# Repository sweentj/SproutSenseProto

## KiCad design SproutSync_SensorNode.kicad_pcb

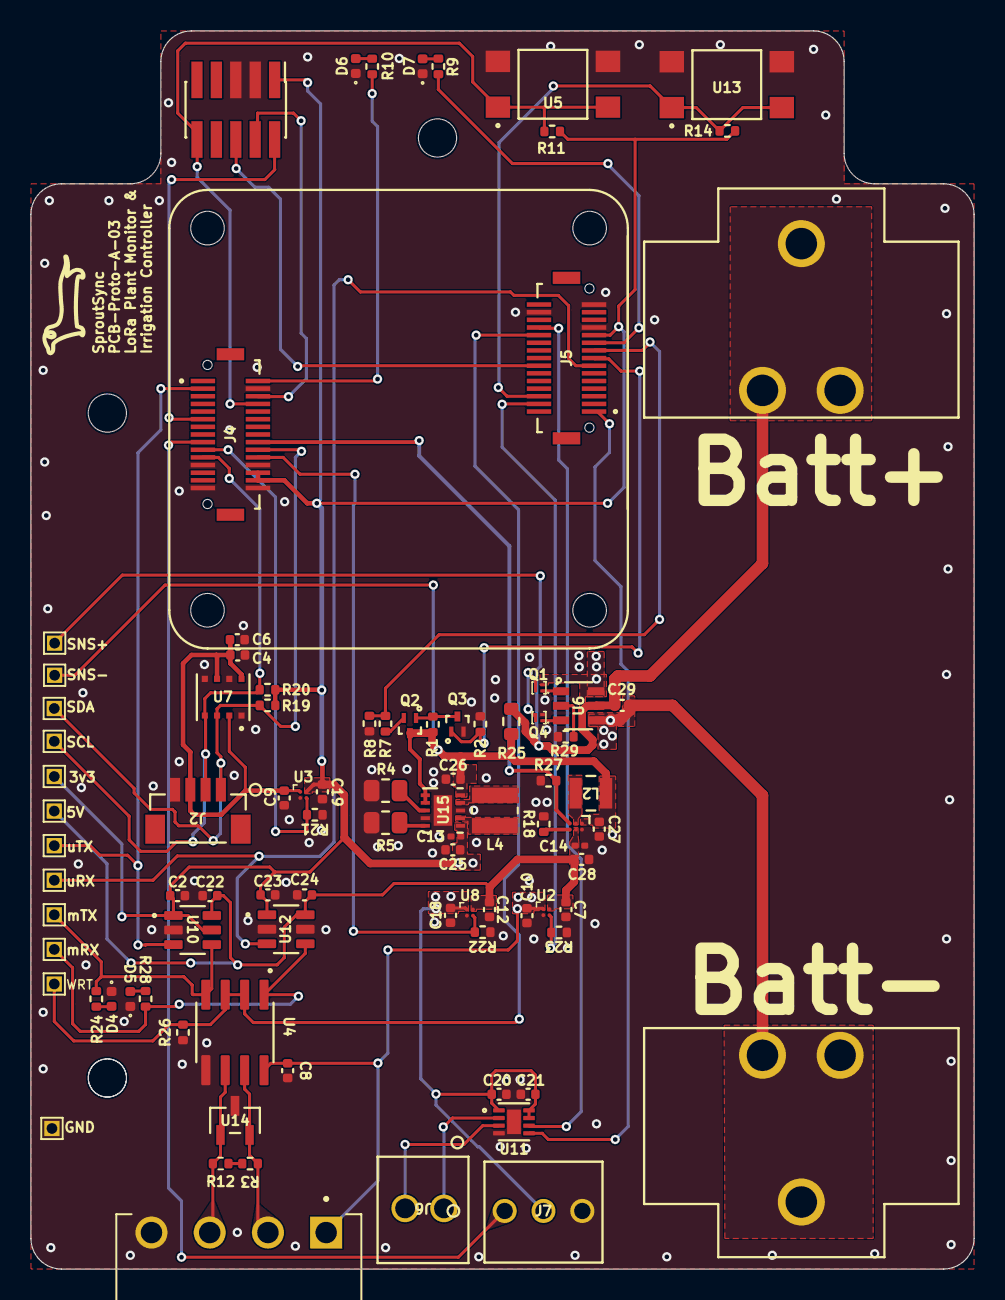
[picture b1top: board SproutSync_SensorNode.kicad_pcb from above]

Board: 2 copper layers, 61.7 x 81.0 mm, 91 parts (0 on the bottom side), 53 nets.

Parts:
C2, C8, C9, C10, C18, C22, C23, C24, C29: 1uF; C_0402_1005Metric
C4, C6, C20, C21: 100nF; C_0402_1005Metric
C7, C12, C19, C25, C26, C27, C28: 22uF; C_0402_1005Metric
C13, C14: 10n; C_0201_0603Metric
D4, D5, D6, D7: B2841USD; LED_0402_1005Metric
J1: TBP02R1-381-04BE; CUI_TBP02R1-381-04BE
J2: BM04B-SRSS-TB; CONN4_BM04B-SRSS_JST
J3, J9: Conn_01x01_Socket; BAT_247
J4, J5: 10132797-031100LF; AMPHENOL_10132797-031100LF
J6: OSTVN02A150; CONN_OSTVN02A150_OST
J7: Conn_01x03; CONN_A-6373-03A_MOL
J8: Conn_ARM_JTAG_SWD_10; PinHeader_2x05_P1.27mm_Vertical_SMD
L2: DFE252012P-1R0M=P2
L4: 2.2u; IND_VLS3012CX-2R2M-1
Q1, Q4: CSD15380F3T; PICOSTAR-3_L0.7-W0.6-P0.35-TL
Q2: SSM3J35MFV; VESM_TOS
Q3: SSM3K16FV; VESM_TOS
R1, R2: 47k; R_0402_1005Metric
R3: 120; R_0402_1005Metric
R4: 36.5k; R_0805_2012Metric
R5: 16.2k; R_0805_2012Metric
R7: 20k; R_0402_1005Metric
R8: 18k; R_0402_1005Metric
R9, R10: 1k; R_0402_1005Metric
R11, R14, R19, R20, R21, R22, R23, R24, R27, R28: 4.7k; R_0402_1005Metric
R12: 0; R_0402_1005Metric
R18: 7.5k; R_0402_1005Metric
R25: 100m; R_0603_1608Metric
R26: 9.31k; R_0402_1005Metric
R29: 330; R_0402_1005Metric
TP1, TP2, TP5, TP6, TP7, TP8, TP9, TP10, TP11, TP12, TP14, TP15: TestPoint; TestPoint_THTPad_1.0x1.0mm_Drill0.5mm
U2, U3, U8: TPS22914BYFPR; YFP4_TEX
U4: SN65HVD3082EDR; SOIC127P599X175-8N
U5, U13: TL3305AF260QG; SW_TL3305AF260QG
U6: S-8240ADZ-M6T1U; SOT-23-6_L2.9-W1.6-P0.95-LS2.8-TL
U7: BME688; IC_BME688
U10, U12: SN74LVC1T45DBVR; SOT95P280X145-6N
U11: DRV8838DSGR; SON50P200X200X80-9N
U14: CDSOT23-SM712; SOT_SM712
U15: TPS63900DSKR; DSK0010A
U16: TPS61299YBHR; DSBGA6_YBH_TEX

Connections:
+3V3: C2.1, C13.1, C19.1, C23.1, C25.1, J4.17, J4.18, J5.11, J8.1 (VTref), R11.2, R14.2, R19.2, R20.2, TP14.1 (1_1), U3.A2 (VIN), U10.1 (VCCA), U10.5 (DIR), U12.1 (VCCA), U15.6 (VOUT)
+5V: C7.1, C12.1, C14.1, C22.1, C24.1, C28.1, TP15.1 (1_1), U2.A2 (VIN), U8.A2 (VIN), U10.6 (VCCB), U12.6 (VCCB), U16.B2 (VOUT)
+BATT: C26.1, C27.1, L2.1, Q2.3 (D), R1.2, R25.2, TP11.1 (1_1), U15.1 (EN), U15.2 (SEL), U15.10 (VIN), U16.A1 (VIN)
/DebugProbe/nRESET: J4.27, J8.10 (~RESET), R11.1, U5.1, U5.2
/PetalStackingConectors/LORA_TX: J4.30, R10.1
/PetalStackingConectors/PAD1: J5.20, R26.2, TP6.1 (1_1), U4.2 (~RE), U4.3 (DE)
/PetalStackingConectors/PAD2: J5.19, U11.6 (PH)
/PetalStackingConectors/PAD4: J5.1, U11.5 (EN)
/PetalStackingConectors/PAD5: J4.9, J7.1
/PetalStackingConectors/PAD6: J4.20, R22.2, U8.B2 (ON)
/PetalStackingConectors/PAD7: J4.10, R21.2, U3.B2 (ON)
/PetalStackingConectors/PAD8: J4.22, R27.2, U16.C1 (EN)
/PetalStackingConectors/PAD14: J4.2, TP2.1 (1_1), U10.3 (A)
/PetalStackingConectors/PAD15: J5.7, TP1.1 (1_1), U12.3 (A)
/PetalStackingConectors/PAD16: J5.28, R14.1, U13.1, U13.2
/PetalStackingConectors/PAD20: J4.28, J8.4 (SWCLK/TCK)
/PetalStackingConectors/PAD21: J4.6, J8.2 (SWDIO/TMS)
/PetalStackingConectors/PAD29: J5.29, R23.2, U2.B2 (ON)
/PetalStackingConectors/PAD32: J5.8, Q3.1 (G), R2.2
/PetalStackingConectors/PAD33: J5.9, R7.1, R8.2
/PetalStackingConectors/PAD35: J5.10, R9.1
/PetalStackingConectors/PAD41: J5.24, J8.6 (SWO/TDO)
/PetalStackingConectors/PAD48: J2.2, J4.11, R20.1, TP10.1 (1_1), U7.4 (SCK)
/PetalStackingConectors/PAD49: J2.1, J4.21, R19.1, TP9.1 (1_1), U7.3 (SDI)
AMB_PWR_3p3: C4.1, C6.1, C9.1, J2.3, U3.A1 (VOUT), U7.2 (CSB), U7.6 (VDDIO), U7.8 (VDD)
GND: C2.2, C4.2, C6.2, C7.2, C8.2, C9.2, C10.2, C12.2, C13.2, C14.2, C18.2, C19.2, C20.2, C21.2, C22.2, C23.2, C24.2, C25.2, C26.2, C27.2, C28.2, D4.1 (K), D5.1 (K), D6.1 (K), D7.1 (K), J1.4, J2.4, J4.12, J4.15, J4.16, J4.19, J4.29, J5.12, J5.15, J5.17, J7.3, J8.3 (GND), J8.5 (GND), Q3.2 (S), Q4.2 (S), R2.1, R4.2, R5.2, R8.1, R18.1, R21.1, R22.1, R23.1, R26.1, R27.1, R29.1, TP7.1 (1_1), U2.B1 (GND), U3.B1 (GND), U4.5 (GND), U5.3, U5.4, U7.1 (GND), U7.5 (SDO), U7.7 (GND__1), U8.B1 (GND), U10.2 (GND), U11.4 (GND), U11.9 (EXP), U12.2 (GND), U12.5 (DIR), U13.3, U13.4, U14.3 (common), U15.4 (CFG2), U15.8 (GND), U15.11 (TP), U16.A2 (GND)
GNDPWR: C29.2, J9.1 (Pin_1_1), Q1.2 (S), U6.4 (NC), U6.6 (VSS)
IRRI_PWR_5p0: C18.1, C20.1, C21.1, J7.2, U8.A1 (VOUT), U11.1 (VM), U11.7 (~SLEEP), U11.8 (VCC)
unnamed: D4.2 (A), R28.1
unnamed: D5.2 (A), R24.1
unnamed: D6.2 (A), R10.2
unnamed: D7.2 (A), R9.2
unnamed: C29.1, J3.1 (Pin_1_1), R25.1, TP8.1 (1_1), U6.5 (VDD)
unnamed: J6.1, U11.2 (OUT1)
unnamed: J6.2, U11.3 (OUT2)
unnamed: Q1.3 (D), Q4.3 (D)
unnamed: Q1.1 (G), U6.1 (DO)
unnamed: Q2.1 (G), Q3.3 (D), R1.1
unnamed: Q2.2 (S), R7.2
unnamed: Q4.1 (G), U6.3 (CO)
unnamed: R3.2, R12.1
unnamed: R29.2, U6.2 (VM)
unnamed: R4.1, U15.3 (CFG1)
unnamed: R5.1, U15.5 (CFG3)
unnamed: L4.1, U15.9 (L1)
unnamed: L4.2, U15.7 (L2)
unnamed: L2.2, U16.B1 (SW)
unnamed: R18.2, U16.C2 (VSEL)
RS485_A+: J1.3, R12.2, U4.6 (A), U14.1 (A1)
RS485_B-: J1.2, R3.1, U4.7 (B), U14.2 (A2)
RX: R28.2, TP12.1 (1_1), U4.1 (R), U12.4 (B)
SOIL_PWR_5p0: C8.1, C10.1, J1.1, U2.A1 (VOUT), U4.8 (VCC)
TX: R24.2, TP5.1 (1_1), U4.4 (D), U10.4 (B)

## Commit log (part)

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2025-07-25 Initial commit for local files
2025-07-31 2nd rev schematic done
2025-08-05 mostly routed
2025-08-05 edited silksceen
2025-08-11 finished rev1
2025-08-25 Removed via in pads
2025-09-17 Swapped H bridge and irrigation conn
2025-09-17 added pin mapping xslx
2025-12-16 updated after bringup
2025-12-16 replaced soil_sns frontend with SN74
2025-12-18 ver2 layout in progress
2025-12-20 rev2 precheck DRC clean
2026-01-02 add diode cathode indicator
2026-02-20 SWD port updated
2026-04-30 updated schematic for pwr savings
2026-05-04 updated pcb for pwr savings
2026-05-05 increased size of BGA pad
2026-05-05 updated BGA to 0.25mm
2026-05-06 added vias
